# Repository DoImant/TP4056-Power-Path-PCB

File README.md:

# Description
A problem with the TP4056 breakout circuit is that the load must be disconnected when the battery is being charged. This is because the charging circuitry detects when the charge current falls below C/10 (constant current charge mode near the end of the charge cycle).
C is the battery capacity in mAh. When a load is connected to the battery, this changes the detected current, allowing the TP4056 to stop charging may never end!

A "bypass" consisting of an additional current path with a diode and a p-channel mosfet can help here. It is a controlled switch that disconnects the battery when an external power supply (e.g. solar cell) is connected.

The idea is that the P-channel FET will disconnect the battery from the load when a power source is connected to the charging chip. The TP4056 still charges the battery, but with no load. The load is directly from the power source powered. With a solar cell, the battery is disconnected when sufficient solar energy is available. If it generates more electricity than the load needs, the battery is also charged.

When the power source is removed, the P-channel FET conducts, connecting the load to the battery.

With this configuration, the TP4056 can safely charge the battery when the load is connected because the battery is charged during application external power supply is disconnected from the load.

The circuit presented here implements the load distribution. The board can be glued to the back of the TP4056-breakout and be connected to the existing soldering pads.

## Connection example

A detailed explanation can be found here:  [detailed explanation](https://www.best-microcontroller-projects.com/tp4056.html)

Have PCBs made: [Aisler](https://aisler.net/p/JAYYOSGH)

## Operation with solar cell
If the TP4056 breakout is operated with a solar cell, the maximum possible charging current must probably be reduced because, for example, 5V solar cells usually cannot deliver 1A charging current. A 2.5W solar cell with 5V generates a maximum charging current of 500mA. The adjustment is made on the TP4056 breakouts by swapping the resistor R3 (1.2kΩ).

|  R3 (kΩ)   | I-Bat (mA) |
| ----------:|-----------:|
|    10      |        130 |
|     5      |        250 |
|     4      |        300 |
|     3      |        400 |
|     2      |        580 |
|     1.66   |        690 |
|     1.50   |        780 |
|     1.33   |        900 |
|     1.20   |       1000 | 

A value between 2kΩ and 3kΩ would be appropriate for a solar cell such as that listed above.

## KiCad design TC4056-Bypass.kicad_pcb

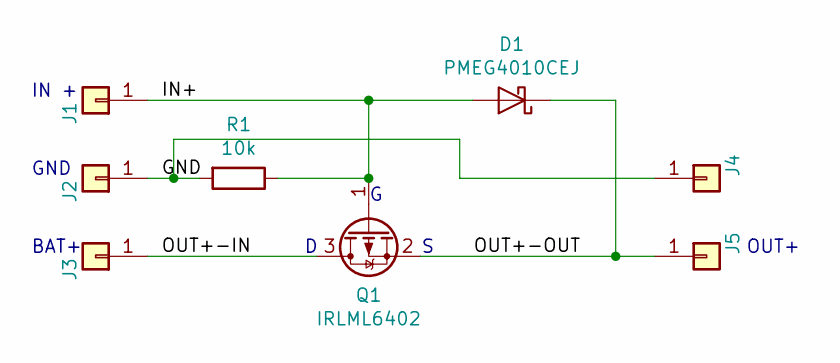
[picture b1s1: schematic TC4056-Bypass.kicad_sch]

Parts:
D1: PMEG4010CEJ; D_SOD-323_HandSoldering
J1, J2, J3, J4, J5: Conn_01x01; SolderWire-0.5sqmm_1x01_D0.9mm_OD2.3mm
Q1: IRLML6402; SOT-23
R1: 10k; R_1206_3216Metric_Pad1.30x1.75mm_HandSolder

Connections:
/GND: J2.1, J4.1, R1.2
/IN+: D1.2 (A), J1.1, Q1.1 (G), R1.1
/OUT+-IN: J3.1, Q1.3 (D)
/OUT+-OUT: D1.1 (K), J5.1, Q1.2 (S)

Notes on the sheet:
IN +
BAT+
OUT+
GND

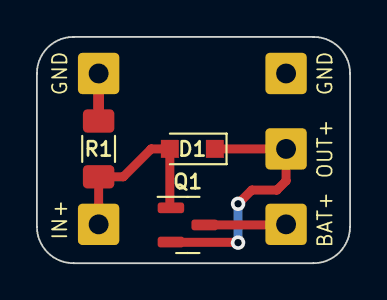
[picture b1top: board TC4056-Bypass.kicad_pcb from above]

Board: 2 copper layers, 17.4 x 12.6 mm, 8 parts (0 on the bottom side), 4 nets.

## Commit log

2022-06-24 README changend
2022-06-24 Readme changed
